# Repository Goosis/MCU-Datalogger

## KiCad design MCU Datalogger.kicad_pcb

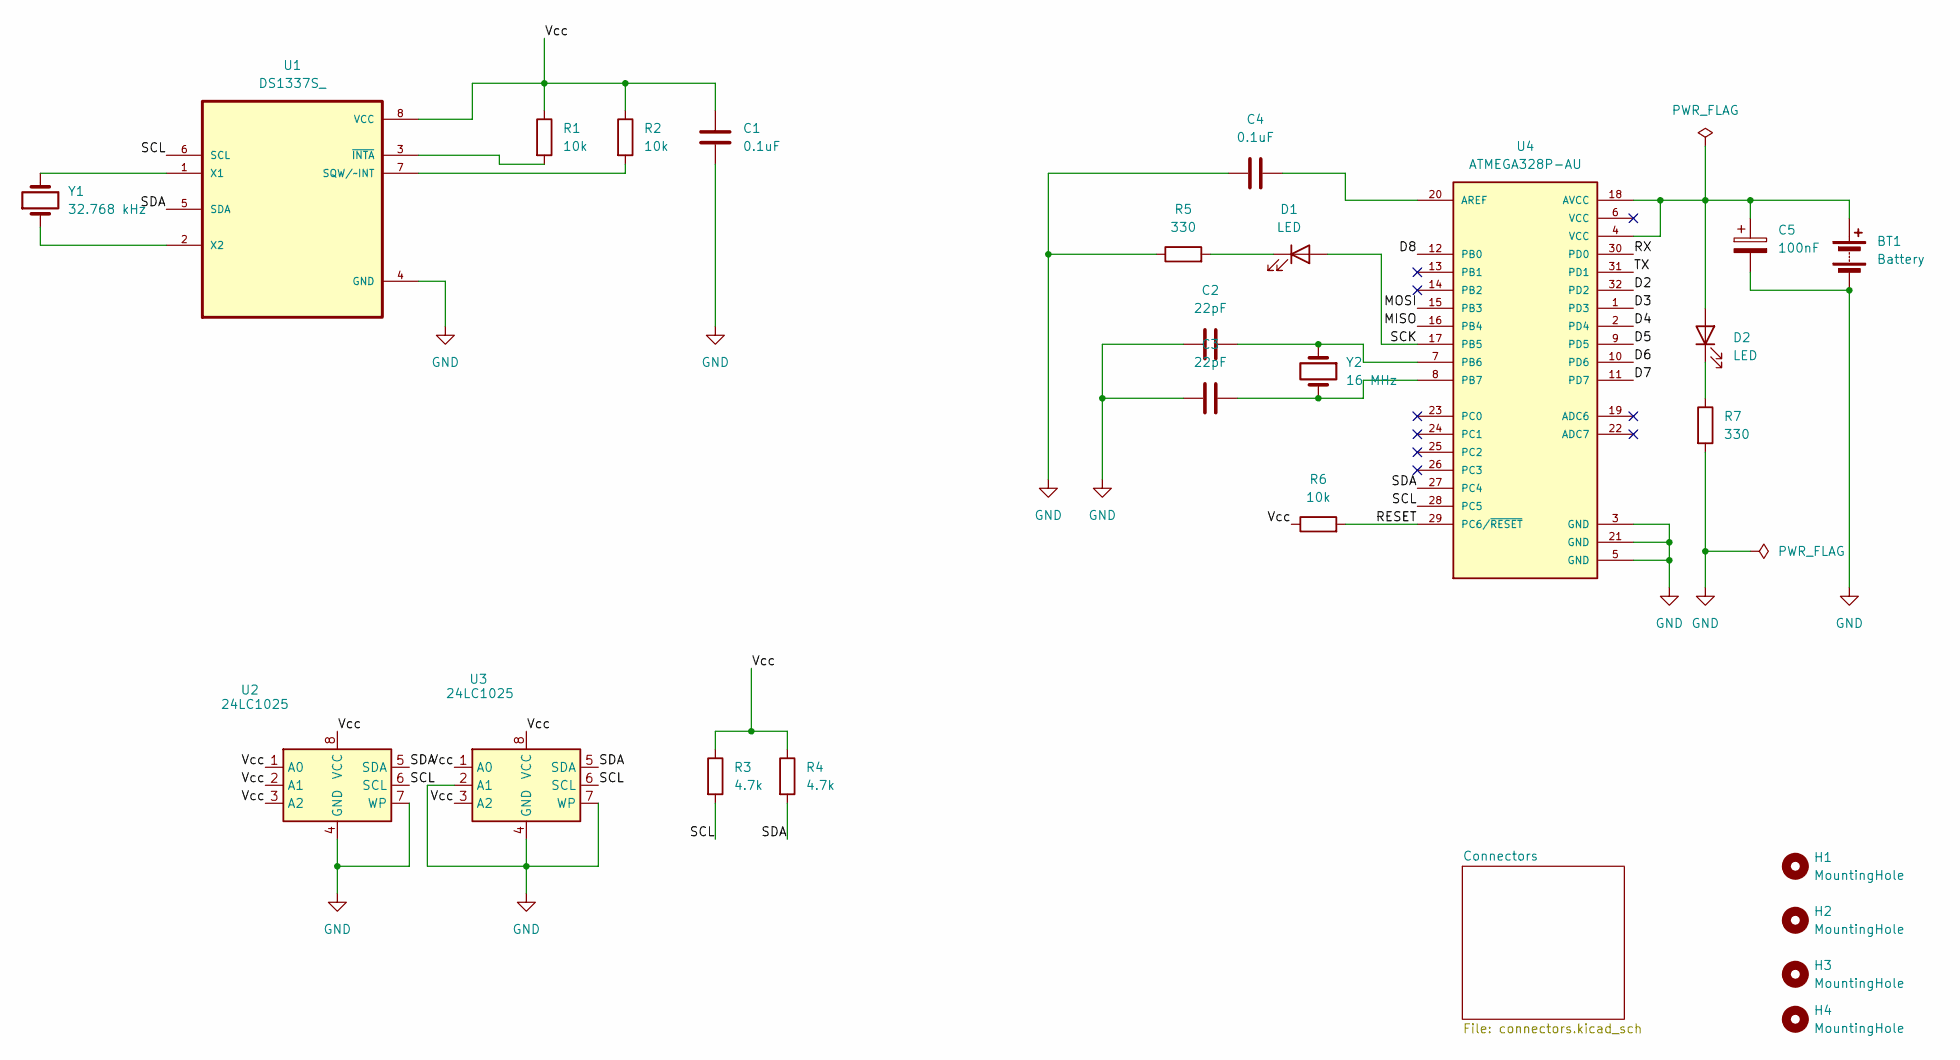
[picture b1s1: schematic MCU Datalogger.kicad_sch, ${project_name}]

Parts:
BT1: Battery; PinHeader_1x02_P2.54mm_Vertical
C1, C4: 0.1uF; C_0805_2012Metric
C2, C3: 22pF; C_0805_2012Metric
C5: 100nF; C_0805_2012Metric
D1, D2: LED; LED_0805_2012Metric
H1, H2, H3, H4: MountingHole; MountingHole_2.1mm
R1, R2, R6: 10k; R_0805_2012Metric
R3, R4: 4.7k; R_0805_2012Metric
R5, R7: 330; R_0805_2012Metric
U1: DS1337S_; SOIC127P600X175-8N
U2, U3: 24LC1025; SOIC-8_5.23x5.23mm_P1.27mm
U4: ATMEGA328P-AU; QFP80P900X900X120-32N; PARTREV 8271A
Y1: 32.768 kHz; Crystal_SMD_5032-2Pin_5.0x3.2mm_HandSoldering
Y2: 16 MHz; Crystal_SMD_5032-2Pin_5.0x3.2mm_HandSoldering

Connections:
/D2: U4.32 (PD2); also elsewhere on the board
/D3: U4.1 (PD3); also elsewhere on the board
/D4: U4.2 (PD4); also elsewhere on the board
/D5: U4.9 (PD5); also elsewhere on the board
/D6: U4.10 (PD6); also elsewhere on the board
/D7: U4.11 (PD7); also elsewhere on the board
/D8: U4.12 (PB0); also elsewhere on the board
/MISO: U4.16 (PB4); also elsewhere on the board
/MOSI: U4.15 (PB3); also elsewhere on the board
/RESET: R6.2, U4.29 (PC6/~RESET); also elsewhere on the board
/RX: U4.30 (PD0); also elsewhere on the board
/SCK: D1.2 (A), U4.17 (PB5)
/SCL: R3.2, U1.6 (SCL), U2.6 (SCL), U3.6 (SCL), U4.28 (PC5); also elsewhere on the board
/SDA: R4.2, U1.5 (SDA), U2.5 (SDA), U3.5 (SDA), U4.27 (PC4); also elsewhere on the board
/TX: U4.31 (PD1); also elsewhere on the board
/Vcc: C1.1, R1.1, R2.1, R3.1, R4.1, R6.1, U1.8 (VCC), U2.1 (A0), U2.2 (A1), U2.3 (A2), U2.8 (VCC), U3.1 (A0), U3.3 (A2), U3.8 (VCC); also elsewhere on the board
GND: BT1.2 (-), C1.2, C2.1, C3.1, C4.1, C5.2, R5.1, R7.2, U1.4 (GND), U2.4 (GND), U2.7 (WP), U3.2 (A1), U3.4 (GND), U3.7 (WP), U4.3 (GND), U4.5 (GND), U4.21 (GND); also elsewhere on the board
unnamed 17: BT1.1 (+), C5.1, D2.2 (A), U4.4 (VCC), U4.18 (AVCC); also elsewhere on the board
unnamed: D1.1 (K), R5.2
unnamed: D2.1 (K), R7.1
unnamed: R2.2, U1.7 (SQW/~INT)
unnamed: U1.1 (X1), Y1.2
unnamed: U1.2 (X2), Y1.1
unnamed: R1.2, U1.3 (~INTA)
unnamed: C4.2, U4.20 (AREF)
unnamed: C2.2, U4.7 (PB6), Y2.1
unnamed: C3.2, U4.8 (PB7), Y2.2

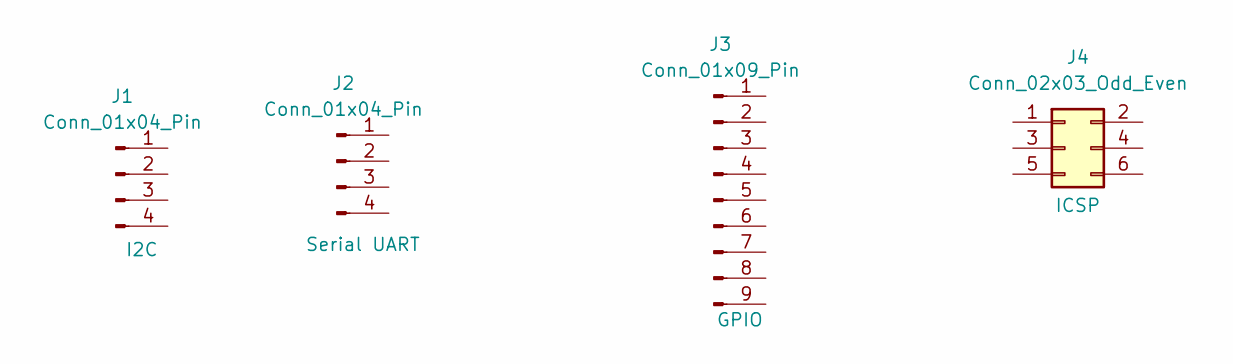
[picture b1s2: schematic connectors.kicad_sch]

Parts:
J1, J2: Conn_01x04_Pin; PinHeader_1x04_P2.54mm_Vertical
J3: Conn_01x09_Pin; PinHeader_1x09_P2.54mm_Vertical
J4: Conn_02x03_Odd_Even; PinHeader_2x03_P2.54mm_Vertical

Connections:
/D2: J3.1; also elsewhere on the board
/D3: J3.2; also elsewhere on the board
/D4: J3.3; also elsewhere on the board
/D5: J3.4; also elsewhere on the board
/D6: J3.5; also elsewhere on the board
/D7: J3.6; also elsewhere on the board
/D8: J3.7; also elsewhere on the board
/MISO: J4.1; also elsewhere on the board
/MOSI: J4.4; also elsewhere on the board
/RESET: J4.5; also elsewhere on the board
/RX: J2.3; also elsewhere on the board
/SCL: J1.4, J4.3; also elsewhere on the board
/SDA: J1.3; also elsewhere on the board
/TX: J2.4; also elsewhere on the board
/Vcc: J1.2, J2.2, J3.9, J4.2; also elsewhere on the board
GND: J1.1, J2.1, J3.8, J4.6; also elsewhere on the board

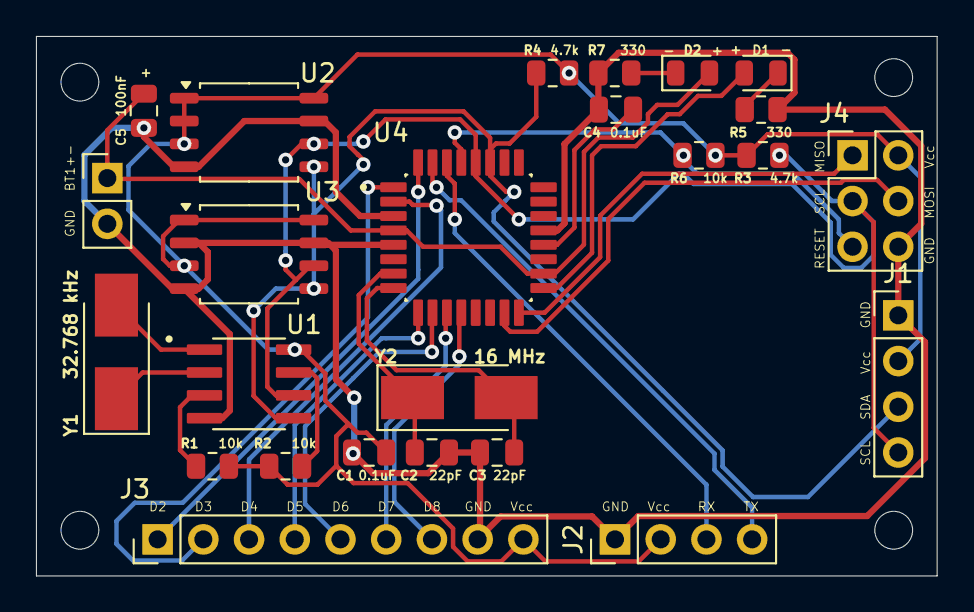
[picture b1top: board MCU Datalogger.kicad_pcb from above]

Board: 2 copper layers, 50.0 x 30.0 mm, 29 parts (0 on the bottom side), 27 nets.

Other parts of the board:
BT1+-: Battery; PinHeader_1x02_P2.54mm_Vertical

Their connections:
GND: BT1+-.2 (-); also elsewhere on the board
unnamed 17: BT1+-.1 (+); also elsewhere on the board

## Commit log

2025-03-10 second commit
2025-03-10 Setup
2025-03-17 Обновил схему и плату
2025-03-19 assigned footprint libraries
2025-03-19 wirred the 1st sheet
2025-03-25 finished project
2025-03-25 saved changes before merge
